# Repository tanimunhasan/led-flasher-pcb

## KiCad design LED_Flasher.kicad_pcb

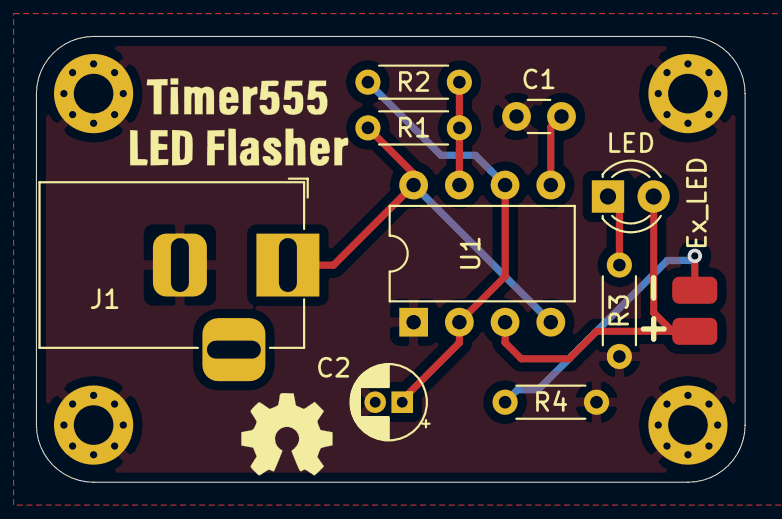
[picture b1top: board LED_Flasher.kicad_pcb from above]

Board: 2 copper layers, 39.4 x 24.8 mm, 14 parts (0 on the bottom side), 8 nets.

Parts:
C1: 100nF; C_Disc_D3.0mm_W1.6mm_P2.50mm
C2: 10uF; CP_Radial_D4.0mm_P1.50mm
Ex_LED: Ex_LED; SolderJumper-2_P1.3mm_Open_Pad1.0x1.5mm
H1, H2, H3, H4: MountingHole_Pad; MountingHole_2.2mm_M2_Pad_Via
J1: Barrel_Jack; BarrelJack_Horizontal
LED: LED; LED_D3.0mm
R1: 150; R_Axial_DIN0204_L3.6mm_D1.6mm_P5.08mm_Horizontal
R2: 72k; R_Axial_DIN0204_L3.6mm_D1.6mm_P5.08mm_Horizontal
R3, R4: 2k; R_Axial_DIN0204_L3.6mm_D1.6mm_P5.08mm_Horizontal
U1: NE555; DIP-8_W7.62mm

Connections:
GND: C1.1, C2.2, H1.1, H2.1, H3.1, H4.1, J1.2, R3.2, R4.2, U1.1
unnamed: C1.2, U1.5
unnamed: LED.1, R3.1
unnamed: Ex_LED.2, R4.1
unnamed: R1.2, R2.1, U1.7
OUT: Ex_LED.1, LED.2, U1.3
TR: C2.1, R2.2, U1.2, U1.6
VDD: J1.1, R1.1, U1.4, U1.8
